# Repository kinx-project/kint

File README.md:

The kinT keyboard controller is a replacement for your Kinesis Advantage or
Advantage 2 ergonomic keyboards.

You can use it for example…

* to build or modify your own keyboard
* to [work around bugs in the standard controller](https://michael.stapelberg.ch/posts/2013-03-21-kinesis_custom_controller/)
* to resurrect a keyboard with a failing Kinesis keyboard controller
* because you prefer to run open source software such as the [QMK firmware](https://docs.qmk.fm/), even on your keyboard

See also:

* [My blog post introducing the kinT keyboard controller](https://michael.stapelberg.ch/posts/2020-07-09-kint-kinesis-keyboard-controller/)
* [My twitch stream recording introducing the kinT keyboard controller](https://youtu.be/I0kwQbnhlfk)

## Quick overview

<table border="0" width="100%">
<tr>
<td width="33%">

3D render (front, LEDs)
</td>
<td width="33%">

3D render (back, components)
</td>
<td width="33%">

schematic
</td>
</tr>
</table>

## Compatibility

The kinT keyboard controller was made for the Kinesis Advantage or Advantage 2
series.

The kinT keyboard controller is not compatible with the newer Kinesis Advantage
360 series, introduced in 2022, because the 360 is a split keyboard that uses an
entirely different form factor for its electronics ([Kinesis 360 teardown
photos](https://photos.app.goo.gl/BwgzHgaTz1RKBjqc6)).

The kinT keyboard controller is also not compatible with **very old Advantage**
keyboards, where the left and right keywell circuit boards plug directly into
the controller. See [issue #42](https://github.com/kinx-project/kint/issues/42)
for details and pictures.

## Building your own kinT keyboard controller

1. Follow [“Buying the board and components (Bill of
   materials)”](https://github.com/kinx-project/kint#buying-the-board-and-components-bill-of-materials). When
   ordering from OSH Park (board) and Digi-Key (components), you’ll get the
   minimum quantity of 3 boards for 72 USD (24 USD per board), and one set of
   components for 49 USD.

   * If you have any special requirements regarding which Teensy microcontroller
     to use, this is the step where you would replace the Teensy 3.6 with your
     choice.

1. Wait for the components to arrive. When ordering from big shops like Digi-Key
   or Mouser, this typically takes 2 days to many places in the world.

1. Wait for the boards to arrive. This takes 6 days in the best case when
   ordering from OSH Park with their Super Swift Service option. In general, the
   longer you are willing to wait, the cheaper it is going to get.

1. Follow [the soldering
   guide](https://github.com/kinx-project/kint#soldering). This will take about
   an hour.

1. [Install the firmware](https://github.com/kinx-project/kint#installing-the-firmware)

## Installing the kinT replacement controller in your Kinesis keyboard

After replacing your existing Kinesis controller with the kinT controller, you have some options with respect to the USB cable:

1. The easiest way is to remove the existing cable from the Kinesis keyboard, and
use a regular USB cable instead (going through the existing hole in the case, no
mod required).

1. If you want to keep using the existing Kinesis cable, you could build the [kinX
open hardware
hub](https://michael.stapelberg.ch/posts/2018-04-17-kinx-usb-hub/), which uses a
compatible connector.

1. Another way is to cut open a USB cable and solder it onto the matching pins of
the Kinesis cable.  You can confirm the pinout in the hardware design files for
the kinX hub. From issue #9, the [7-pin variant](https://github.com/kinx-project/kint/issues/9#issuecomment-751507493) and the [9-pin variant](https://github.com/kinx-project/kint/issues/9#issuecomment-774753427).

1. And yet one more option is to use a right angle USB dashboard extension instead of the Kinesis cable as described in [this issue #9 comment](https://github.com/kinx-project/kint/issues/9#issuecomment-1434304973). You would then plug a regular USB cable into this extension.

## Why use the kinT instead of the older replacement board?

* The kinT supports both, the older Kinesis Advantage (KB500) **and** the newer
  Kinesis Advantage 2 (KB600) keyboards. They differ in how the thumb pads are
  connected. See the soldering instructions below.

   * NOTE: If this is the *only* feature you’re interested in, and you already
     have a custom keyboard controller for your older Kinesis, [check out the
     u6w5 adapter
     board](https://github.com/kinx-project/adapter-use-kb600-with-kb500-controller)
     I made!

* The kinT is made for the newer Teensy 3.x and 4.x series, which will remain
  widely available for years to come, whereas the [Teensy++ 2.0 is
  discontinued](https://www.pjrc.com/store/teensypp.html).

* The kinT is a smaller PCB (4.25 x 3.39 inches, or 108.0 x 86.1 mm), which makes it:

   * more compact: can be inserted/removed without having to unscrew a key well.

   * cheaper: 72 USD for 3 boards at oshpark, instead of 81 USD.

* The kinT silkscreen
  ([front](https://raw.githubusercontent.com/kinx-project/kint/44e6c8be96a0e1e13ada5eafdeba8c51a2d6c9e8/pcb-3d-render-front-v2020-06-23.png),
  [back](https://raw.githubusercontent.com/kinx-project/kint/44e6c8be96a0e1e13ada5eafdeba8c51a2d6c9e8/pcb-3d-render-back-v2020-06-23.png))
  and
  [schematic](https://github.com/kinx-project/kint/blob/44e6c8be96a0e1e13ada5eafdeba8c51a2d6c9e8/schematic-v2020-06-23.pdf)
  are much much clearer, making assembly a breeze.

* The kinT is a good starting point for your own project:

   * kinT was designed in the open source [KiCad](https://kicad.org/)
     program, meaning you do not need any license subscriptions.

   * The clear silkscreen and schematic make development and debugging easier.

* On the kinT, the Teensy no longer has to be soldered onto the board upside down.

* On the kinT, the FPC connectors have been moved for less strain on the cables.

* The kinT makes possible lower-cost builds: if you don’t need the scroll lock,
  num lock and keypad LEDs, you can use a Teensy LC for merely 11 USD.

## Compatibility: which Teensy to use?

The kinT keyboard controller was made for the Teensy 3.x and 4.x series of
devices, which are ARM based.

The older Atmel based Teensy++ 2.0 are also supported, but they require cutting
one set of solder jumpers and closing a second set, to account for clashing pin
assignments.

Which Teensy should you buy for your build? Here are a few considerations:

* I have been using the Teensy 4.1 for many months without problems.

* I used the Teensy 3.6 for multiple years, and many others are happy with it,
  too.

* The Teensy++ 2.0 used to be the most popular choice, in part because it was
  the only option with the the predecessor keyboard controller. The [Teensy++
  2.0 is discontinued](https://www.pjrc.com/store/teensypp.html), so I would no
  longer recommend it for new keyboard builds.

* If you are an advanced user of the QMK firmware, note that despite QMK working
  on the Teensy 3.6, [some features are not yet
  ported/working](https://github.com/kinx-project/kint/issues/10). As QMK was
  originally made for AVR micro controllers, you will likely find best overall
  QMK feature availability with the older Teensy++ 2.0.

### Reference: full Teensy compatibility chart

TODO: add power consumption as a column. relevant for using the keyboard with a laptop on the go

| teensy         | LEDs | Cost   | input latency | clock speed | MCU         | QMK                                                                   |
|----------------|------|--------|---------------|-------------|-------------|-----------------------------------------------------------------------|
| teensy++ 2.0   | yes  | $24.00 | 3.27ms        | 16 MHz AVR  | AT90USB1286 | 0.13.17 or newer                                                      |
| ~~teensy 3.0~~ | no   |        |               | 48 MHz M4   | MK20DX128   | untested                                                              |
| ~~teensy 3.1~~ | no   |        |               |             | MK20DX256   | untested                                                              |
| teensy LC      | no   | $11.65 | ?             | 48 MHz M0+  |             | [development version](https://github.com/qmk/qmk_firmware/pull/17301) |
| teensy 3.2     | no   | $19.80 | ?             | 72 MHz M4   |             | [development version](https://github.com/qmk/qmk_firmware/pull/25013) |
| teensy 3.5     | yes  | $24.25 | ?             | 120 MHz M4F | MK64FX      | unlikely ([interest?](https://github.com/kinx-project/kint/issues/3)) |
| teensy 3.6     | yes  | $29.25 | 1.97ms        | 180 MHz M4F | MK66FX      | 0.14.0 or newer                                                       |
| teensy 4.0     | no   | $19.95 | 0.9ms         | 600 MHz M7  | MIMXRT1062  | 0.14.0 or newer                                                       |
| teensy 4.1     | yes  | $26.85 | 0.9ms         | 600 MHz M7  | MIMXRT1062  | 0.14.0 or newer                                                       |

See [this blog post for more details on keyboard input
latency](https://michael.stapelberg.ch/posts/2021-05-08-keyboard-input-latency-qmk-kinesis/).

## Buying the board and components (Bill of materials)

To buy the board, you can:

* [order the kinT controller from OSH Park](https://oshpark.com/shared_projects/YSZAuKc0) starting at 72 USD
* [order the kinT controller from Aisler](https://aisler.net/p/JQIIIJSL) starting at 18 EUR
* [order the kinT controller from JLCPCB](https://github.com/kinx-project/kint/tree/main/gerbers/jlcpcb)
* or upload the [kint.kicad_pcb
  file](https://github.com/kinx-project/kint/blob/main/kicad/kint.kicad_pcb)
  to the manufacturing service you prefer.

To buy the components, check out the [kinT BOM in the Octopart BOM
tool](https://octopart.com/bom-tool/4AnOAR3f), from where you can conveniently
buy all components via Digi-Key or Mouser.

For your convenience, this is the full BOM (links go to Octopart):

| Part Number                                                                               | Count | Cost   | Description               | Note                                               |
|-------------------------------------------------------------------------------------------|-------|--------|---------------------------|----------------------------------------------------|
| [Teensy 3.6](https://octopart.com/dev-14057-sparkfun-76356774?r=sp)                       | 1     | $32.5  |                           | [your choice!](#compatibility-which-teensy-to-use) |
| [Würth 61301011121](https://octopart.com/61301011121-w%C3%BCrth+elektronik-18818159?r=sp) | 8     | $0.89  | 10 position 2.54mm header | 6 for Teensy<br>2 for KB500<br>0 for KB600         |
| [Molex 39-53-2135](https://octopart.com/39-53-2135-molex-7670149?r=sp)                    | 6     | $1.24  | 13 position FPC connector | 4 for KB500<br>6 for KB600                         |
| [Kingbright APT3216QBC/D](https://octopart.com/apt3216qbc%2Fd-kingbright-5355642?r=sp)    | 4     | $0.47  | 1206 SMD LED              | blue 470nm<br>chose your color!                    |
| [Vishay CRCW120610K0FKEAC](https://octopart.com/crcw120610k0fkeac-vishay-20811529)        | 4     | $0.10  | 1206 10K resistor         | value determines LED brightness                    |
|                                                                                           |       | $48.45 |                           |                                                    |

Note: with all parts (except for the Molex 39-53-2135 FPC connector), there is
no need to get the specific versions from the BOM above — if you have LEDs,
resistors and pin headers still lying around from other projects, feel free to
re-use them!

Note: if you lost the original ribbon cables, you can get a compatible
replacement from [Digikey (Molex 13 Position FFC, FPC Cable 0.049" (1.25mm)
3.000"
(76.20mm))](https://www.digikey.co.uk/en/products/detail/molex/0151680815/4143332),
which is slightly longer than the original (CivLux E208903 - AWM 20960 105C 300V
VW-1), but seems to work well.

## Soldering

All the soldering connections on the kinT keyboard controller are easy to make,
so the whole assembly can be done at home, with a cheap soldering iron and basic
electronic hobby equipment. A build takes about 1 hour of time and involves a
little over 100 soldering connections.

For example, I used the [Miniware TS100 soldering
iron](https://hackaday.com/2017/07/24/review-ts100-soldering-iron/), which can
be found for 50-60 EUR or USD.

If you’re new to soldering, check out [this excellent soldering reference card
from adafruit](https://twitter.com/zekjur/status/952596267884056576).

You can also [watch me solder a kinT keyboard controller on live
stream](https://youtu.be/I0kwQbnhlfk?t=5880) (from 1:38:00 to 3:33:53). The
process can be done in under an hour if you’re not talking to a live audience at
the same time :-). I want to add an edited and higher-quality video, too.

### Soldering instructions for the Teensy 3.x or 4.x

1. Populate the FPC connectors J2, J3, J4, J7 (all keyboards) and J1, J8 for the
   newer Advantage 2 (KB600). Turn the board around and solder all their pins.

1. Solder resistors R1, R2, R3, R4 and the four LEDs onto the board.

   * LEDs are directional parts! Their marker marks the cathode, which is
     labeled as C on the kinT. For details about the marker, refer to the LED
     datasheet, e.g. the [Kingbright APT3216QBC/D data
     sheet](https://www.kingbrightusa.com/images/catalog/SPEC/APT3216QBC-D.pdf)
     if you are using the LED from the [Bill of Materials
     (BOM)](#buying-the-board-and-components-bill-of-materials).

   * If you’re new to SMD (Surface Mount Devices) soldering, check out [How to
     Hand Solder SMD](http://www.davidhaillant.com/smd-soldering/), which
     explains what I call the “One pad at a time” method.

1. Turn the board around and place (but don’t solder) **3 rows of pin headers**
   (top, bottom, vertical) in the Teensy holes.

   * The vertical pin header is required for powering the LEDs.

   * If you want your Teensy to be removable, you can use socket headers here
     instead. [See the instructions below](#using-socket-headers).

1. Place your Teensy on top of the pin header and solder all its pins.

1. Turn the board around and solder all the pin header pins.

1. For the older Advantage (KB500) keyboard, populate pin headers J5, J6 and
   solder their pins.

### Soldering instructions for the Teensy++ 2.0

Follow the [instructions for the Teensy 3.x or 4.x
above](#soldering-instructions-for-the-teensy-3x-or-4x), and then:

1. Using a small knife such as a hobby knife, cut the traces between the pads
   of jumpers JP4, JP5, and JP6. This will disconnect pin 7, pin 15 and pin 16.

   * If you haven't cut traces like this before, SparkFun has a [brief
     illustrated tutorial][jumper-tut] about working with jumpers that is a
     good reference.

2. Close the solder jumpers JP1, JP2, JP3. These will remap pin 7, pin 15 and
   pin 16 onto pins that can be used with the Teensy++ 2.0.

If you are [using socket headers](#using-socket-headers) so that the Teensy is
removable, you can later upgrade to a Teensy 3.x or 4.x by desoldering JP1,
JP2, and JP3, and reclosing the jumpers JP4, JP5, and JP6.

[jumper-tut]: https://learn.sparkfun.com/tutorials/how-to-work-with-jumper-pads-and-pcb-traces/what-is-a-jumper

### Using socket headers

Due to the space for the USB cable in the back, there's not enough room in the
case for a standard socket header, but there are low-profile pin headers that
do fit. [These square-pin socket headers][short-sockets] and [pins][short-pins]
with 0.180" (4.57mm) insulation height have been verified to fit in the KB500,
and will probably fit the KB600 as well. Round "Swiss-style" headers may also
work, but make sure to get the appropriate matching pins for whatever socket
you order.

To build with socket headers, follow the [standard instructions
above](#soldering-instructions-for-the-teensy-3x-or-4x), but instead of the
steps involving soldering the pin headers, do the following:

1. Turn the board around and solder **3 rows of socket headers** (top, bottom,
   vertical) in the Teensy holes on the kinT board.

1. Place and solder the corresponding **3 rows of pin headers** (top, bottom,
   vertical) on the Teensy itself.

1. Insert the Teensy into the sockets.

[short-sockets]: https://octopart.com/slw-124-01-t-s-samtec-292526?r=sp
[short-pins]: https://octopart.com/tsw-124-23-g-s-samtec-274217?r=sp

## Installing the firmware

You can use the QMK Configurator online build tool to compile the QMK firmware for
your kinT keyboard controller, or customize your layout.

Alternatively, you can install the pre-built, tested firmware file (default QMK
keymap and settings) we offer, for example to test whether issues are related to
your self-compiled firmware.

| Teensy           | QMK Configurator                                                                                                                                         | pre-built, tested firmware                                                                                                              |
|------------------|----------------------------------------------------------------------------------------------------------------------------------------------------------|-----------------------------------------------------------------------------------------------------------------------------------------|
| Teensy++ 2.0     | [QMK Configurator (kint2pp)](https://config.qmk.fm/#/kinesis/kint2pp/LAYOUT)                                                                             | [kinesis_kint2pp_default.hex](https://github.com/kinx-project/kint/blob/main/default-firmware/kinesis_kint2pp_default.hex) (2020-07-09) |
| Teensy 3.6       | [QMK Configurator (kint36)](https://config.qmk.fm/#/kinesis/kint36/LAYOUT)                                                                               | [kinesis_kint36_default.hex](https://github.com/kinx-project/kint/blob/main/default-firmware/kinesis_kint36_default.hex) (2020-07-09)   |
| Teensy 4.0 / 4.1 | [QMK Configurator (kint41)](https://config.qmk.fm/#/kinesis/kint41/LAYOUT)  | [kinesis_kint41_default.hex](https://github.com/kinx-project/kint/blob/main/default-firmware/kinesis_kint41_default.hex) (QMK 0.17.9)   |

You can install these .hex files with the [Teensy
Loader](https://www.pjrc.com/teensy/loader.html).

To compile your own firmware, see [QMK: Get
Started](https://docs.qmk.fm/#/?id=get-started) and refer to the [full Teensy
compatibility chart](#reference-full-teensy-compatibility-chart) above to find
the QMK branch to work with.

TIP: When you flash your Teensy you'll be asked to press the reset button. The first time you flash, you'll need to press the push button on the Teensy itself. Default keyboard layouts map this ability to the Kinesis <kbd>progm</kbd> key. So for subsequent flashes, you can press the <kbd>progm</kbd> key instead.

## Debugging / Troubleshooting

### General technique: highlight connections in KiCad

1. Install [KiCad](https://kicad.org/) (free and open source)
1. Clone https://github.com/kinx-project/kint/ and open `kicad/kint.pro` in KiCad
1. Select `Tools` → `Edit PCB`
1. Select `View` → `Flip Board View`, because the front side of kinT contains the LEDs, the back side contains the connectors.
1. Select `Highlight Net`, the second icon from the top in the right icon bar.
   In KiCad 6, the icon is gone. Instead, hold the `Ctrl` key while clicking on the net.
1. Click on the pin of interest. In the bottom left, you’ll see the Net Name (e.g. `COL_3`), and KiCad will highlight all connected traces.

### Issue: LEDs not working

See also [Example issue #13](https://github.com/kinx-project/kint/issues/13) for
a full debugging walk-through.

* Check the orientation of your LEDs, as they are directional parts.

   * The marker printed on the kinT board marks the LED cathode, which is
     labeled as C on the kinT. For details about the marker, refer to the LED
     datasheet, e.g. the [Kingbright APT3216QBC/D data
     sheet](https://www.kingbrightusa.com/images/catalog/SPEC/APT3216QBC-D.pdf)
     if you are using the LED from the [Bill of Materials
     (BOM)](#buying-the-board-and-components-bill-of-materials).

* If your Teensy is not soldered yet (or removed from its socket), you can test your LEDs with a multimeter:
   * switch your multimeter to diode test mode
   * place the black probe (`COM`) on e.g. Teensy pin 12 (`LED_CAPS_LOCK`)
   * place the red probe on the anode (A) of your LED
   * the LED should light up now, or it might be defective:

* Measure that the LED pins behave as expected, e.g. Teensy pin 12 for `LED_CAPS_LOCK`:
   * you should measure 3.3V when the LED is turned off
   * you should measure 0V when the LED is turned on

* Check that you soldered in the vertical pin header, which supplies 3.3V to the LEDs:

### Issue: Keys not working
If groups of keys are not responding, recheck that you've inserted cables straight and deep into each Molex connector before fully closing the connector.

See also [issue #16](https://github.com/kinx-project/kint/issues/16) for
a full debugging walk-through of key issues.

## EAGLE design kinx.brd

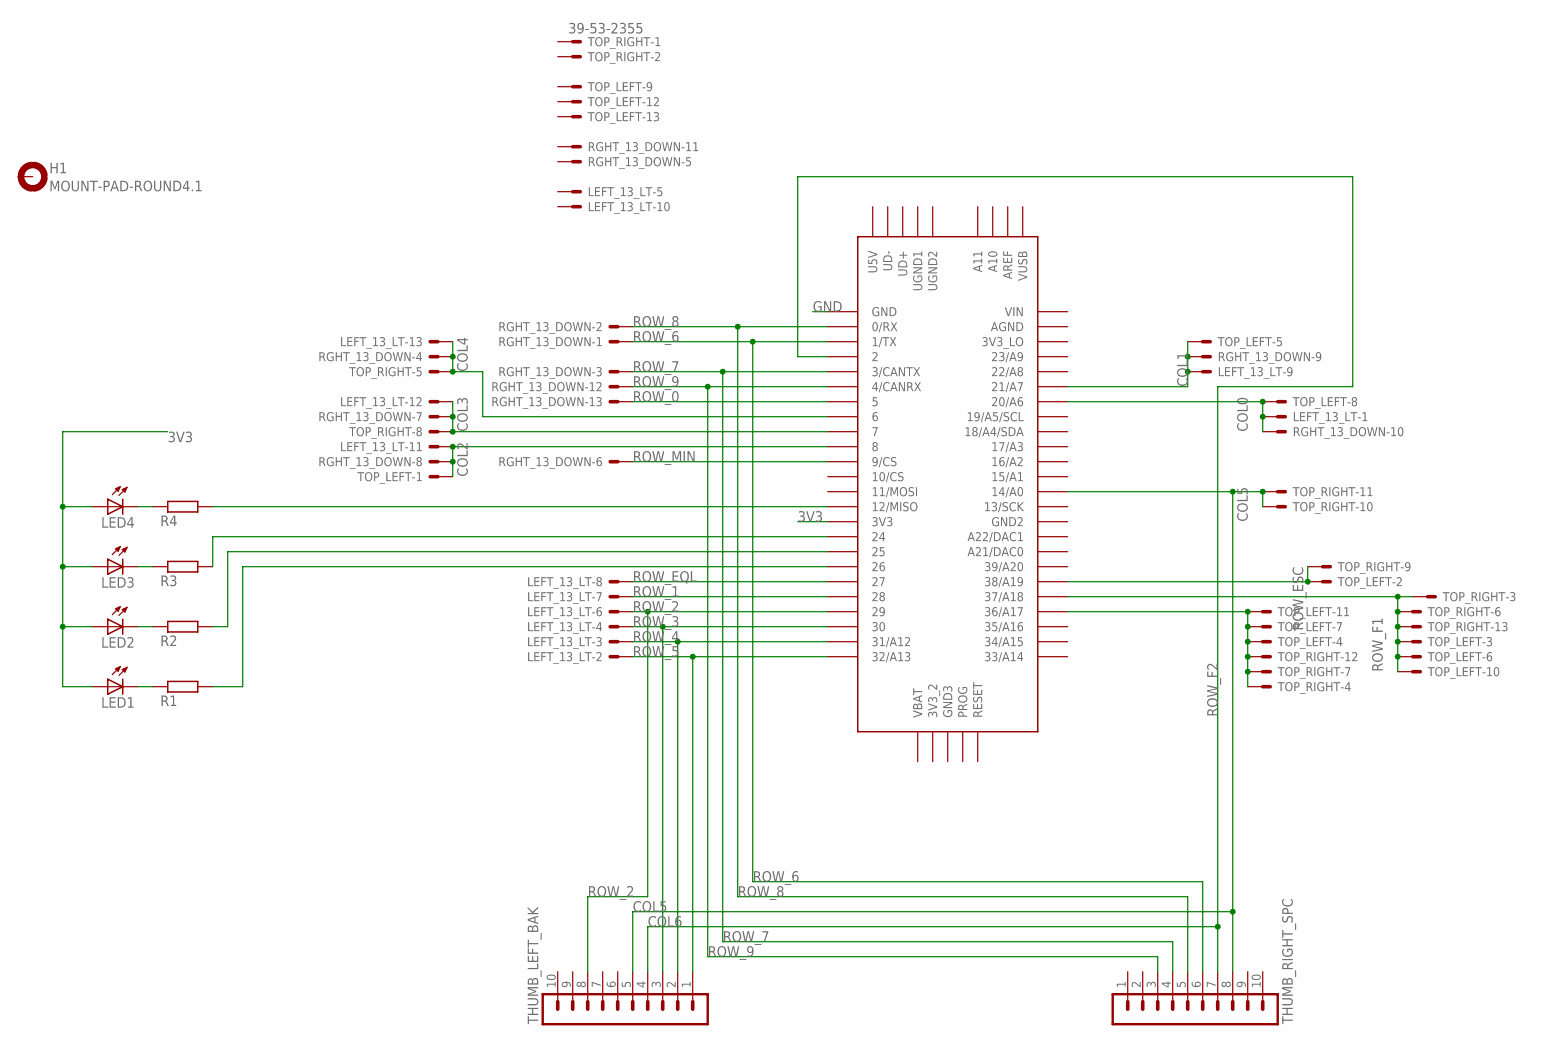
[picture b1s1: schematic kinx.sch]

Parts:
H1: MOUNT-PAD-ROUND4.1; 4,1-PAD
LED1, LED2, LED3, LED4: LEDSML1206; SML1206
LEFT_13_LT: 39-53-2355; 39-53-2135
R1, R2, R3, R4: R-EU_R1206; R1206
RGHT_13_DOWN: 39-53-2355; 39-53-2135
THUMB_LEFT_BAK: MA10-1
THUMB_RIGHT_SPC: MA10-1
TOP_LEFT: 39-53-2355; 39-53-2135
TOP_RIGHT: 39-53-2355; 39-53-2135
U1: TEENSY_3.5/3.6

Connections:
3V3: LED1.A, LED2.A, LED3.A, LED4.A, U1.3V3
COL0: LEFT_13_LT.P$1, RGHT_13_DOWN.P$10, TOP_LEFT.P$8, U1.20/A6
COL1: LEFT_13_LT.P$9, RGHT_13_DOWN.P$9, TOP_LEFT.P$5, U1.21/A7
COL2: LEFT_13_LT.P$11, RGHT_13_DOWN.P$8, TOP_LEFT.P$1, U1.8
COL3: LEFT_13_LT.P$12, RGHT_13_DOWN.P$7, TOP_RIGHT.P$8, U1.7
COL4: LEFT_13_LT.P$13, RGHT_13_DOWN.P$4, TOP_RIGHT.P$5, U1.6
COL5: THUMB_LEFT_BAK.5, THUMB_RIGHT_SPC.8, TOP_RIGHT.P$10, TOP_RIGHT.P$11, U1.14/A0
COL6: THUMB_LEFT_BAK.4, THUMB_RIGHT_SPC.7, U1.2
GND: U1.GND
unnamed: R4.2, U1.12/MISO
unnamed: R3.2, U1.24
unnamed: R2.2, U1.25
unnamed: R1.2, U1.26
unnamed: LED4.C, R4.1
unnamed: LED3.C, R3.1
unnamed: LED2.C, R2.1
unnamed: LED1.C, R1.1
ROW_0: RGHT_13_DOWN.P$13, U1.5
ROW_1: LEFT_13_LT.P$7, U1.28
ROW_2: LEFT_13_LT.P$6, THUMB_LEFT_BAK.8, U1.29
ROW_3: LEFT_13_LT.P$4, THUMB_LEFT_BAK.3, U1.30
ROW_4: LEFT_13_LT.P$3, THUMB_LEFT_BAK.2, U1.31/A12
ROW_5: LEFT_13_LT.P$2, THUMB_LEFT_BAK.1, U1.32/A13
ROW_6: RGHT_13_DOWN.P$1, THUMB_RIGHT_SPC.6, U1.1/TX
ROW_7: RGHT_13_DOWN.P$3, THUMB_RIGHT_SPC.4, U1.3/CANTX
ROW_8: RGHT_13_DOWN.P$2, THUMB_RIGHT_SPC.5, U1.0/RX
ROW_9: RGHT_13_DOWN.P$12, THUMB_RIGHT_SPC.3, U1.4/CANRX
ROW_EQL: LEFT_13_LT.P$8, U1.27
ROW_ESC: TOP_LEFT.P$2, TOP_RIGHT.P$9, U1.38/A19
ROW_F1: TOP_LEFT.P$3, TOP_LEFT.P$6, TOP_LEFT.P$10, TOP_RIGHT.P$3, TOP_RIGHT.P$6, TOP_RIGHT.P$13, U1.37/A18
ROW_F2: TOP_LEFT.P$4, TOP_LEFT.P$7, TOP_LEFT.P$11, TOP_RIGHT.P$4, TOP_RIGHT.P$7, TOP_RIGHT.P$12, U1.36/A17
ROW_MIN: RGHT_13_DOWN.P$6, U1.9/CS

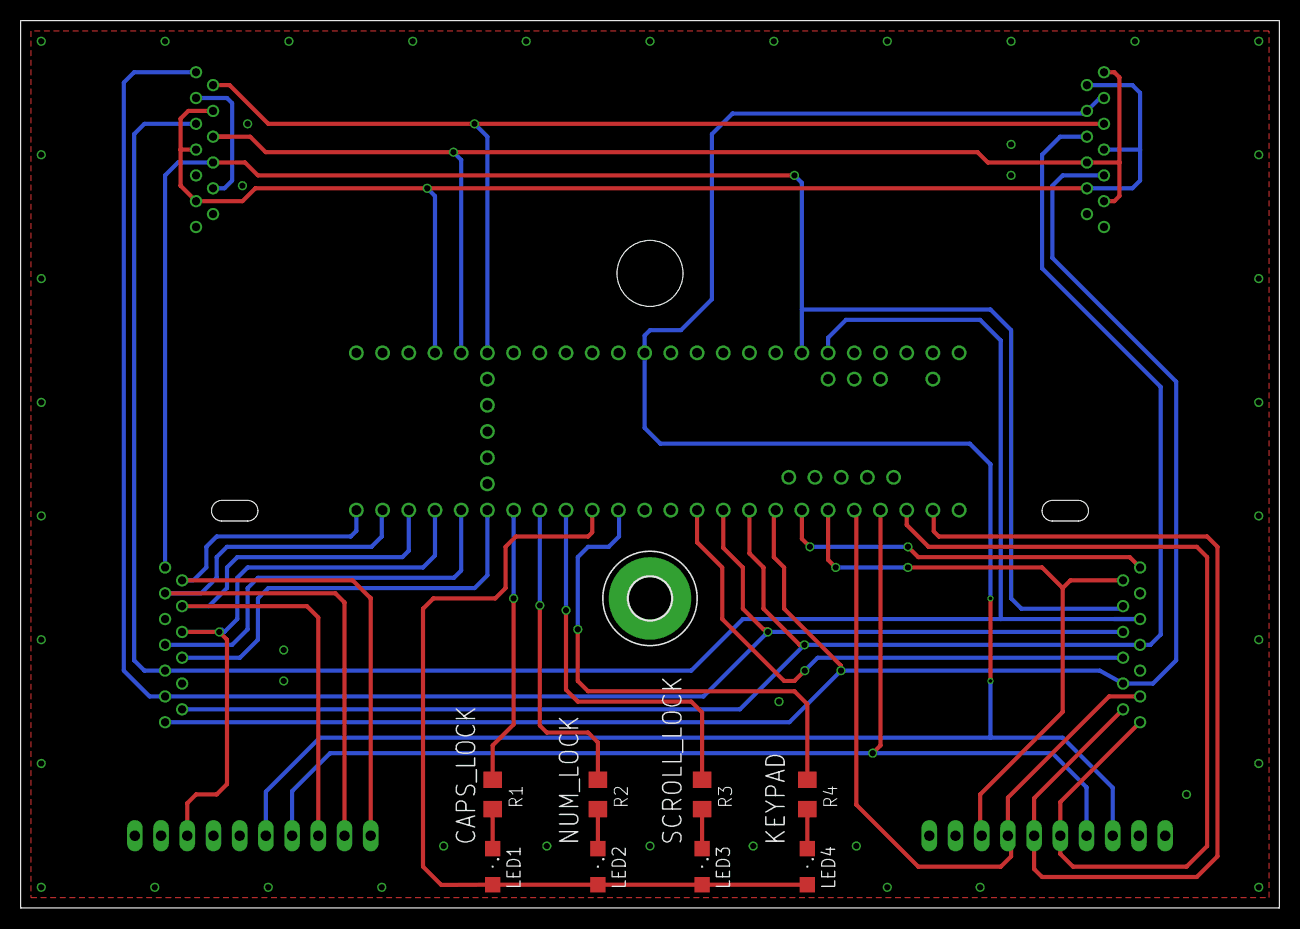
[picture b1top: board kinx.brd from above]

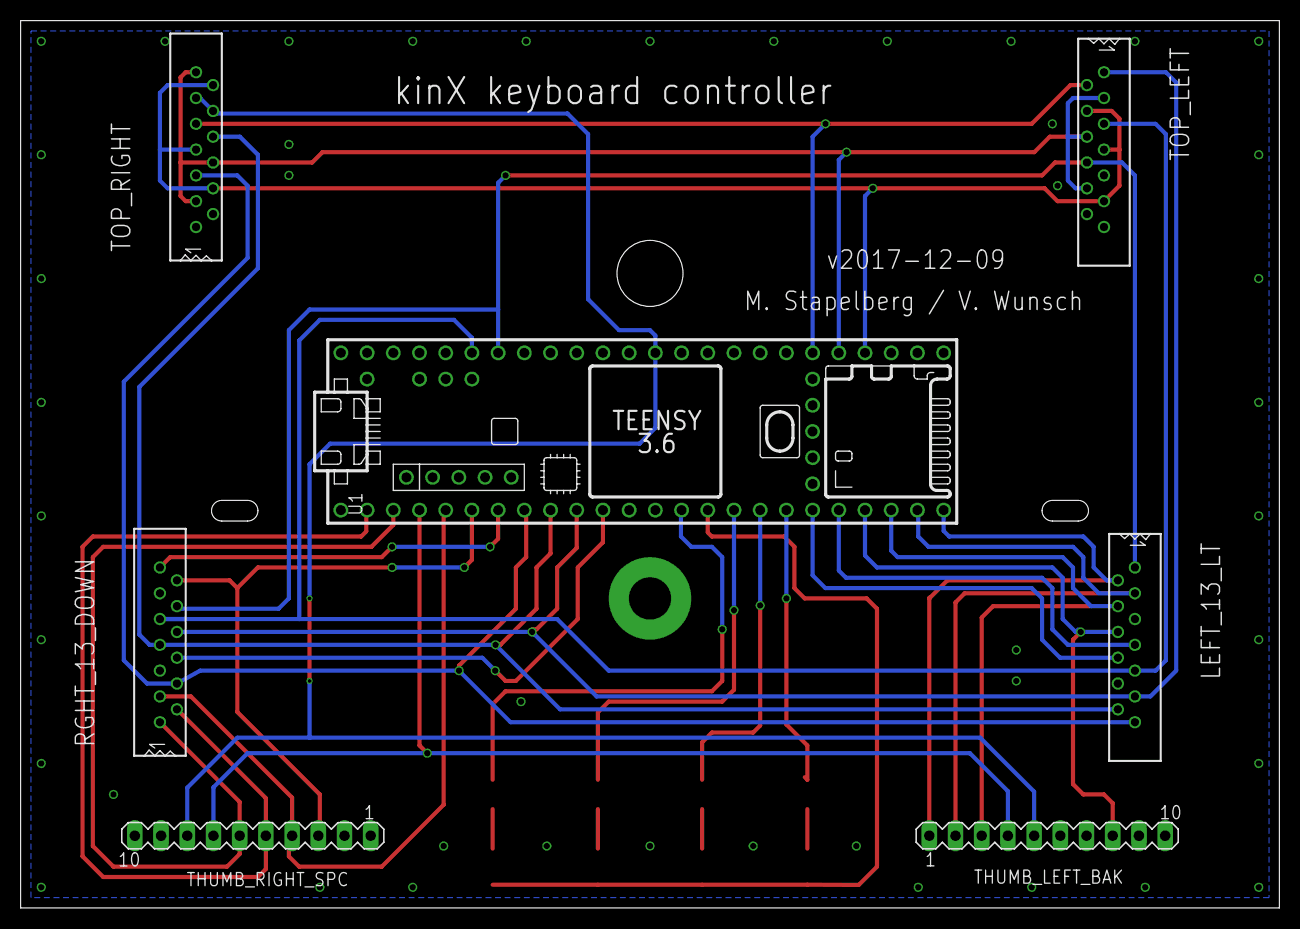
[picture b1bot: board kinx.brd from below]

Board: 2 copper layers, 122.0 x 86.0 mm, 16 parts (7 on the bottom side), 31 nets.

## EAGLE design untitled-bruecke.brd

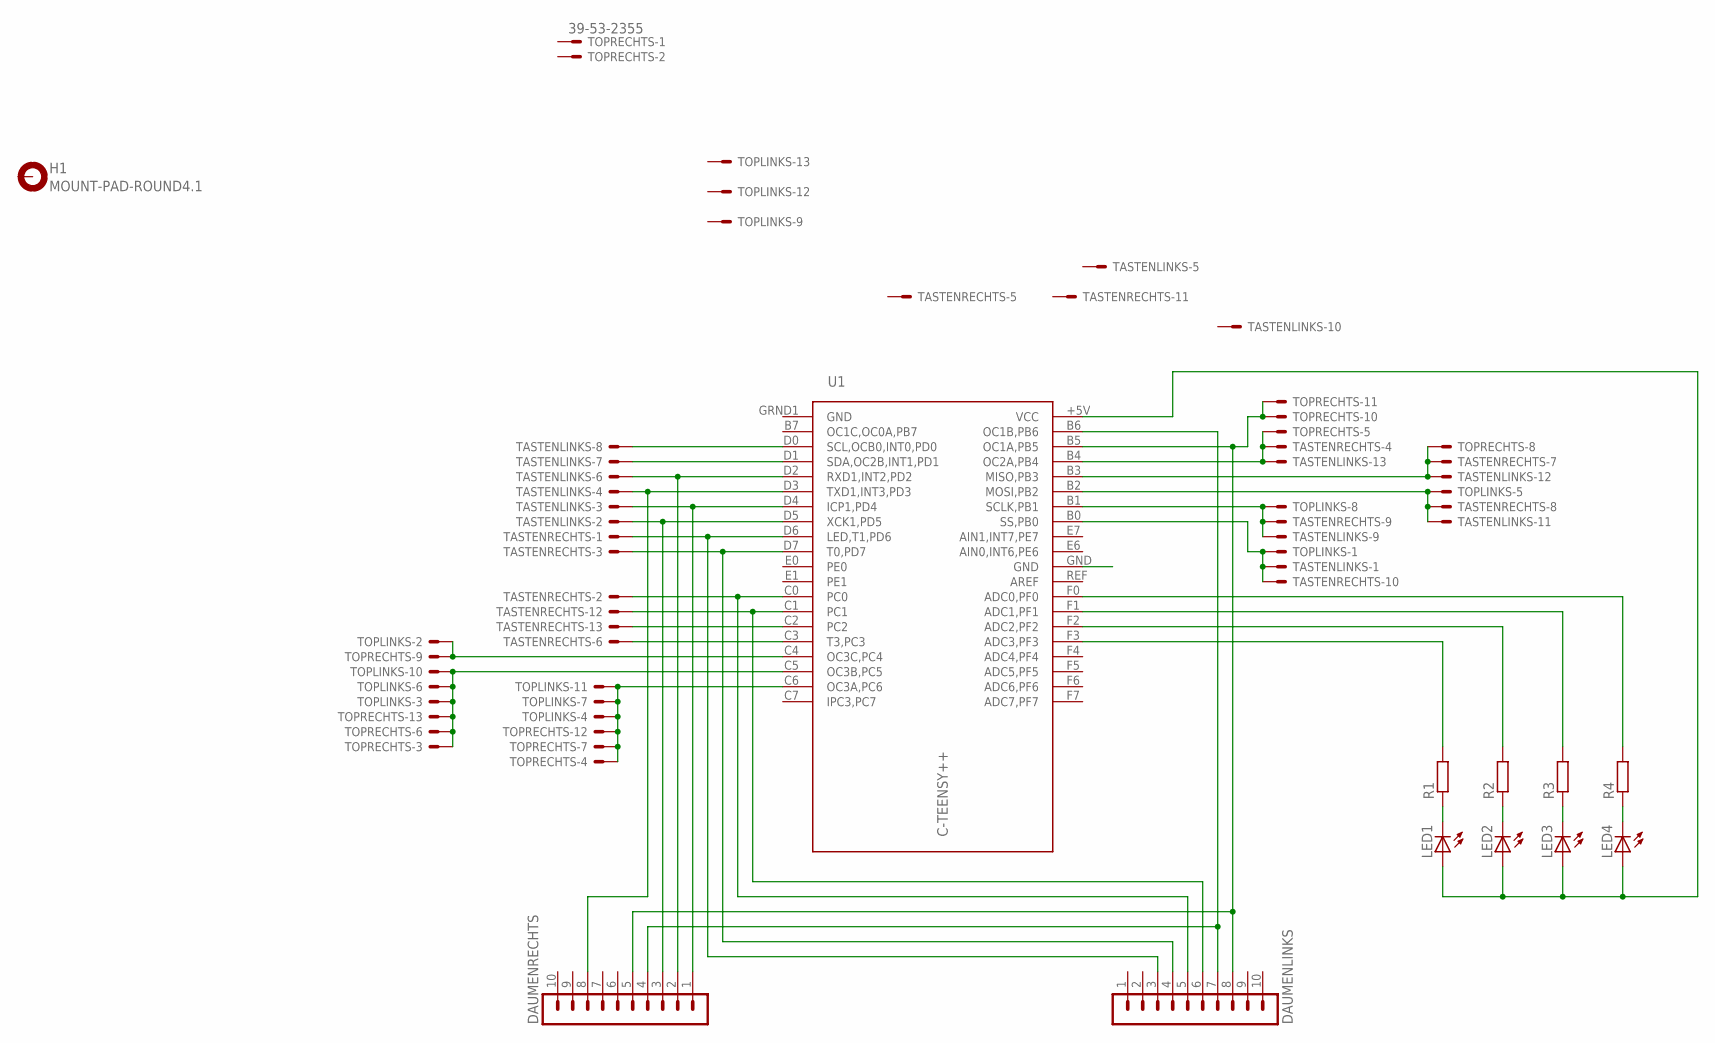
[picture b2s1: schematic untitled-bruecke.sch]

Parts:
DAUMENLINKS: MA10-1
DAUMENRECHTS: MA10-1
H1: MOUNT-PAD-ROUND4.1; 4,1-PAD
LED1, LED2, LED3, LED4: LED3MM
R1, R2, R3, R4: R-EU_R1206; R1206
TASTENLINKS: 39-53-2355; 39-53-2135
TASTENRECHTS: 39-53-2355; 39-53-2135
TOPLINKS: 39-53-2355; 39-53-2135
TOPRECHTS: 39-53-2355; 39-53-2135
U1: C-TEENSY++; TEENSY++

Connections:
B0: TASTENLINKS.P$1, TASTENRECHTS.P$10, TOPLINKS.P$1, U1.B0 (SS,PB0)
B1: TASTENLINKS.P$9, TASTENRECHTS.P$9, TOPLINKS.P$8, U1.B1 (SCLK,PB1)
B2: TASTENLINKS.P$11, TASTENRECHTS.P$8, TOPLINKS.P$5, U1.B2 (MOSI,PB2)
B3: TASTENLINKS.P$12, TASTENRECHTS.P$7, TOPRECHTS.P$8, U1.B3 (MISO,PB3)
B4: TASTENLINKS.P$13, TASTENRECHTS.P$4, TOPRECHTS.P$5, U1.B4 (OC2A,PB4)
B5: DAUMENLINKS.8, DAUMENRECHTS.5, TOPRECHTS.P$10, TOPRECHTS.P$11, U1.B5 (OC1A,PB5)
B6: DAUMENLINKS.7, DAUMENRECHTS.4, U1.B6 (OC1B,PB6)
C0: DAUMENLINKS.5, TASTENRECHTS.P$2, U1.C0
C1: DAUMENLINKS.6, TASTENRECHTS.P$12, U1.C1
C2: TASTENRECHTS.P$13, U1.C2
C3: TASTENRECHTS.P$6, U1.C3 (T3,PC3)
C4: TOPLINKS.P$2, TOPRECHTS.P$9, U1.C4 (OC3C,PC4)
C5: TOPLINKS.P$3, TOPLINKS.P$6, TOPLINKS.P$10, TOPRECHTS.P$3, TOPRECHTS.P$6, TOPRECHTS.P$13, U1.C5 (OC3B,PC5)
C6: TOPLINKS.P$4, TOPLINKS.P$7, TOPLINKS.P$11, TOPRECHTS.P$4, TOPRECHTS.P$7, TOPRECHTS.P$12, U1.C6 (OC3A,PC6)
D0: TASTENLINKS.P$8, U1.D0 (SCL,OCB0,INT0,PD0)
D1: TASTENLINKS.P$7, U1.D1 (SDA,OC2B,INT1,PD1)
D2: DAUMENRECHTS.2, TASTENLINKS.P$6, U1.D2 (RXD1,INT2,PD2)
D3: DAUMENRECHTS.8, TASTENLINKS.P$4, U1.D3 (TXD1,INT3,PD3)
D4: DAUMENRECHTS.1, TASTENLINKS.P$3, U1.D4 (ICP1,PD4)
D5: DAUMENRECHTS.3, TASTENLINKS.P$2, U1.D5 (XCK1,PD5)
D6: DAUMENLINKS.3, TASTENRECHTS.P$1, U1.D6 (LED,T1,PD6)
D7: DAUMENLINKS.4, TASTENRECHTS.P$3, U1.D7 (T0,PD7)
GND: U1.GRND1 (GND)
unnamed: R1.2, U1.F3 (ADC3,PF3)
unnamed: R2.2, U1.F2 (ADC2,PF2)
unnamed: R3.2, U1.F1 (ADC1,PF1)
unnamed: R4.2, U1.F0 (ADC0,PF0)
unnamed: LED1.A, LED2.A, LED3.A, LED4.A, U1.+5V (VCC)
unnamed: LED4.K (C), R4.1
unnamed: LED3.K (C), R3.1
unnamed: LED2.K (C), R2.1
unnamed: LED1.K (C), R1.1

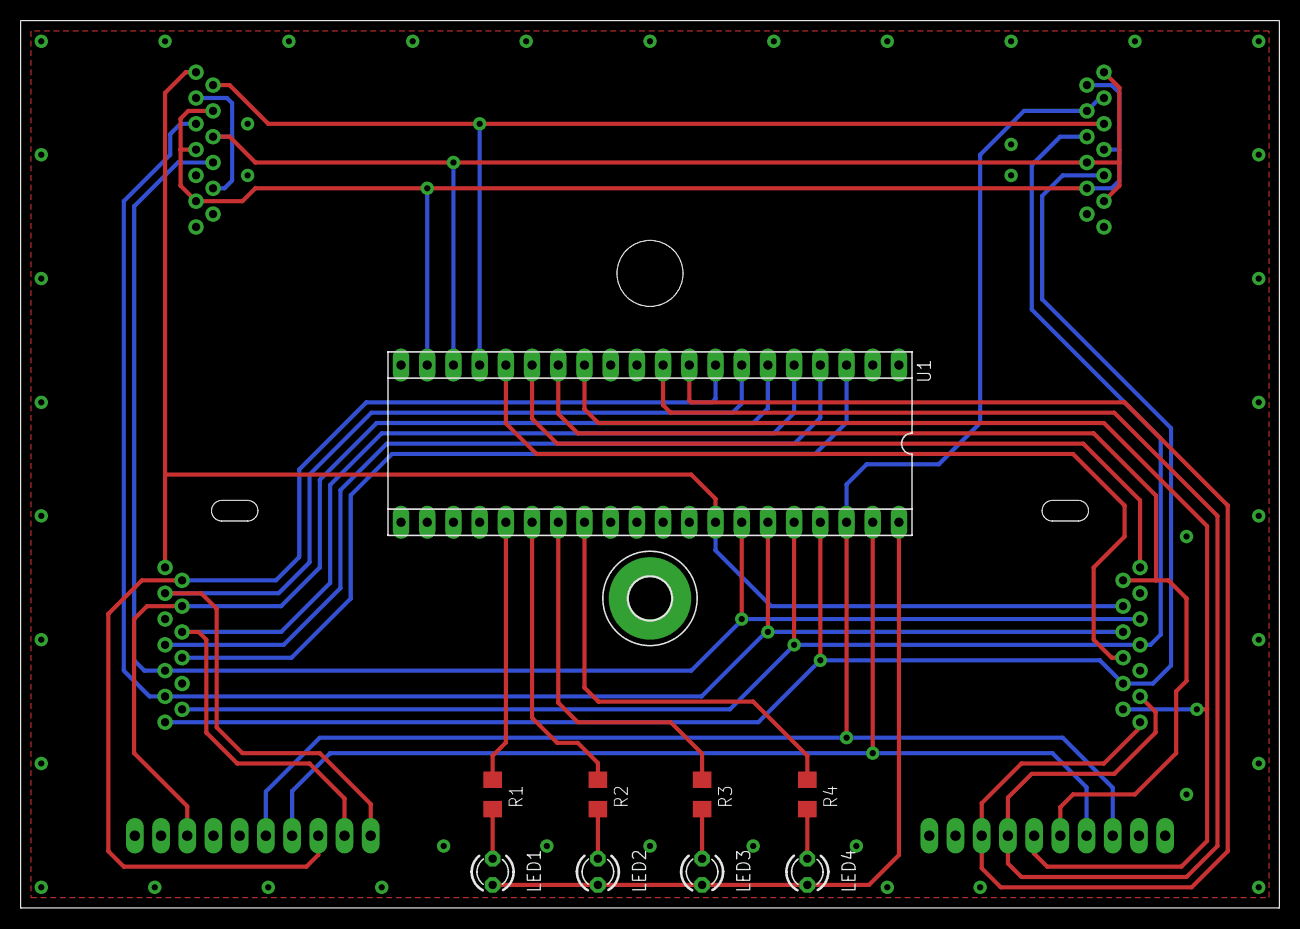
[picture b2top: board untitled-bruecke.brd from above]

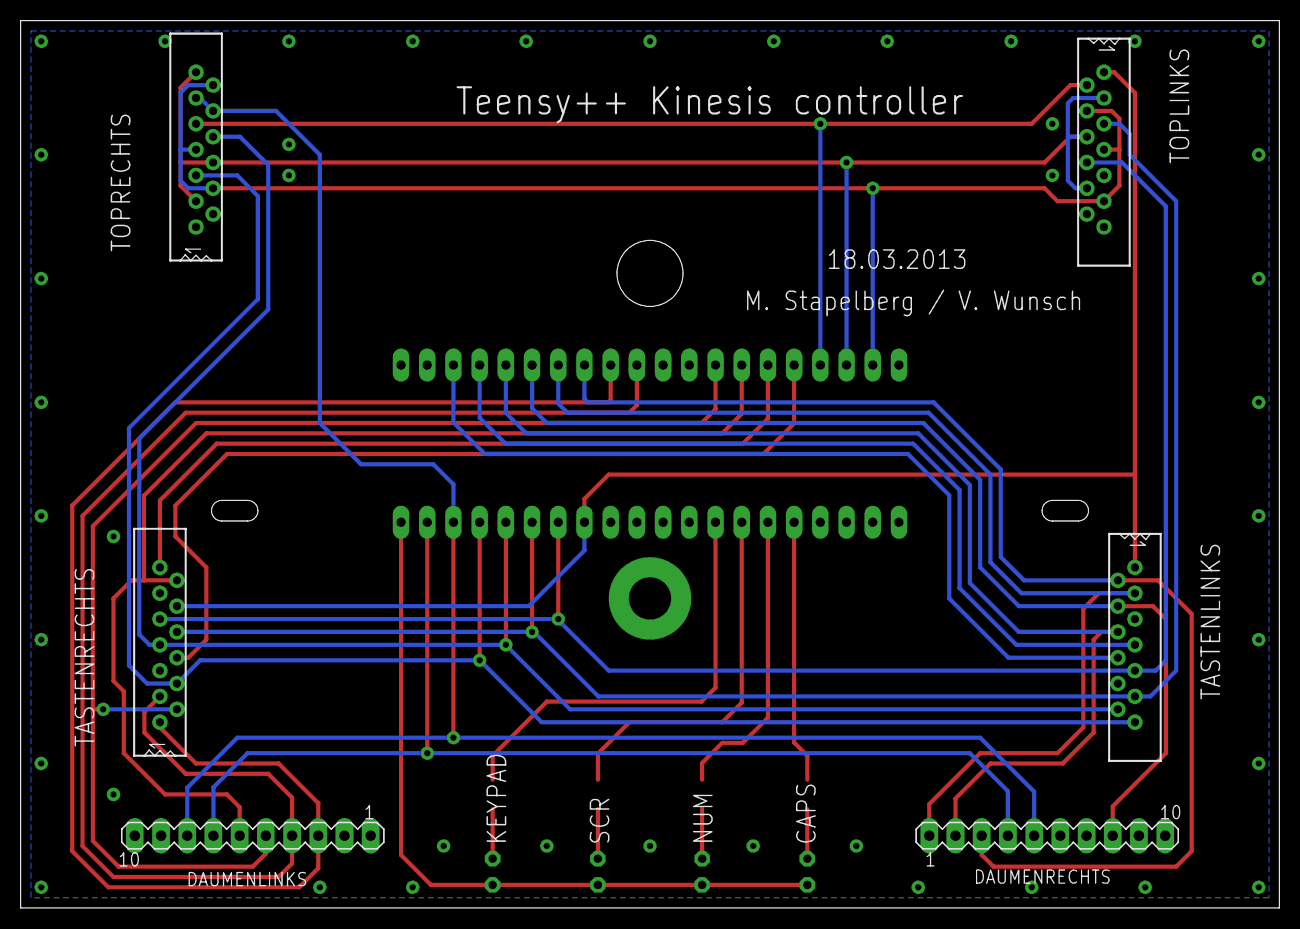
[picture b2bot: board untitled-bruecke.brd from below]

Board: 2 copper layers, 122.0 x 86.0 mm, 16 parts (6 on the bottom side), 31 nets.

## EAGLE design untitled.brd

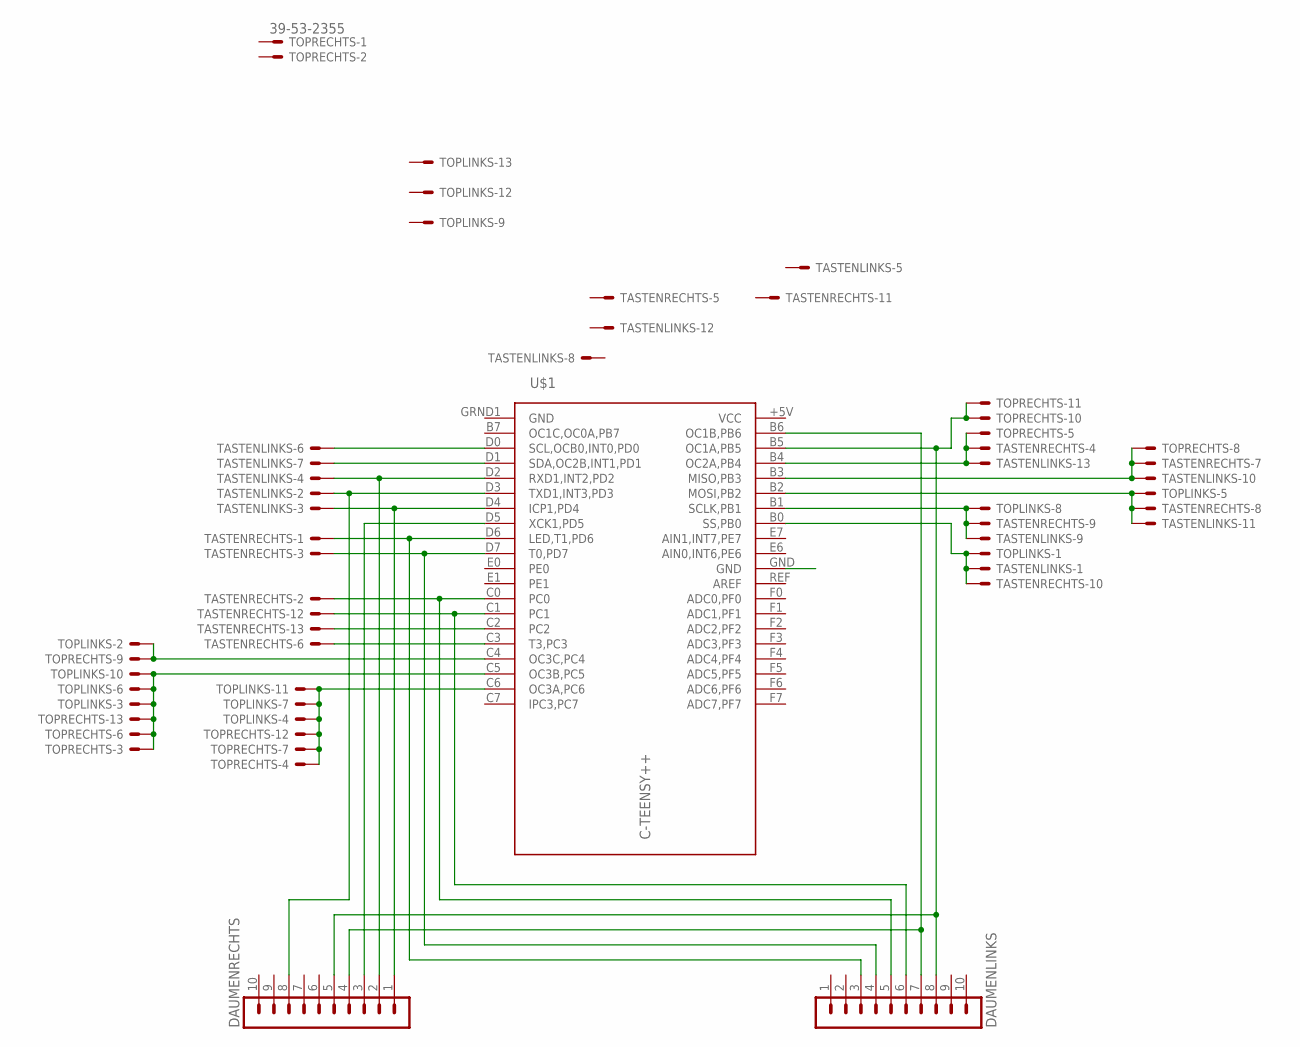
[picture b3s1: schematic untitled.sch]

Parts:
DAUMENLINKS: MA10-1
DAUMENRECHTS: MA10-1
TASTENLINKS: 39-53-2355; 39-53-2135
TASTENRECHTS: 39-53-2355; 39-53-2135
TOPLINKS: 39-53-2355; 39-53-2135
TOPRECHTS: 39-53-2355; 39-53-2135
U$1: C-TEENSY++; TEENSY++

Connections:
B0: TASTENLINKS.P$1, TASTENRECHTS.P$10, TOPLINKS.P$1, U$1.B0 (SS,PB0)
B1: TASTENLINKS.P$9, TASTENRECHTS.P$9, TOPLINKS.P$8, U$1.B1 (SCLK,PB1)
B2: TASTENLINKS.P$11, TASTENRECHTS.P$8, TOPLINKS.P$5, U$1.B2 (MOSI,PB2)
B3: TASTENLINKS.P$10, TASTENRECHTS.P$7, TOPRECHTS.P$8, U$1.B3 (MISO,PB3)
B4: TASTENLINKS.P$13, TASTENRECHTS.P$4, TOPRECHTS.P$5, U$1.B4 (OC2A,PB4)
B5: DAUMENLINKS.8, DAUMENRECHTS.5, TOPRECHTS.P$10, TOPRECHTS.P$11, U$1.B5 (OC1A,PB5)
B6: DAUMENLINKS.7, DAUMENRECHTS.4, U$1.B6 (OC1B,PB6)
C0: DAUMENLINKS.5, TASTENRECHTS.P$2, U$1.C0
C1: DAUMENLINKS.6, TASTENRECHTS.P$12, U$1.C1
C2: TASTENRECHTS.P$13, U$1.C2
C3: TASTENRECHTS.P$6, U$1.C3 (T3,PC3)
C4: TOPLINKS.P$2, TOPRECHTS.P$9, U$1.C4 (OC3C,PC4)
C5: TOPLINKS.P$3, TOPLINKS.P$6, TOPLINKS.P$10, TOPRECHTS.P$3, TOPRECHTS.P$6, TOPRECHTS.P$13, U$1.C5 (OC3B,PC5)
C6: TOPLINKS.P$4, TOPLINKS.P$7, TOPLINKS.P$11, TOPRECHTS.P$4, TOPRECHTS.P$7, TOPRECHTS.P$12, U$1.C6 (OC3A,PC6)
D0: TASTENLINKS.P$6, U$1.D0 (SCL,OCB0,INT0,PD0)
D1: TASTENLINKS.P$7, U$1.D1 (SDA,OC2B,INT1,PD1)
D2: DAUMENRECHTS.2, TASTENLINKS.P$4, U$1.D2 (RXD1,INT2,PD2)
D3: DAUMENRECHTS.8, TASTENLINKS.P$2, U$1.D3 (TXD1,INT3,PD3)
D4: DAUMENRECHTS.1, TASTENLINKS.P$3, U$1.D4 (ICP1,PD4)
D5: DAUMENRECHTS.3, U$1.D5 (XCK1,PD5)
D6: DAUMENLINKS.3, TASTENRECHTS.P$1, U$1.D6 (LED,T1,PD6)
D7: DAUMENLINKS.4, TASTENRECHTS.P$3, U$1.D7 (T0,PD7)
GND: U$1.GRND1 (GND)
VCC: U$1.+5V (VCC)

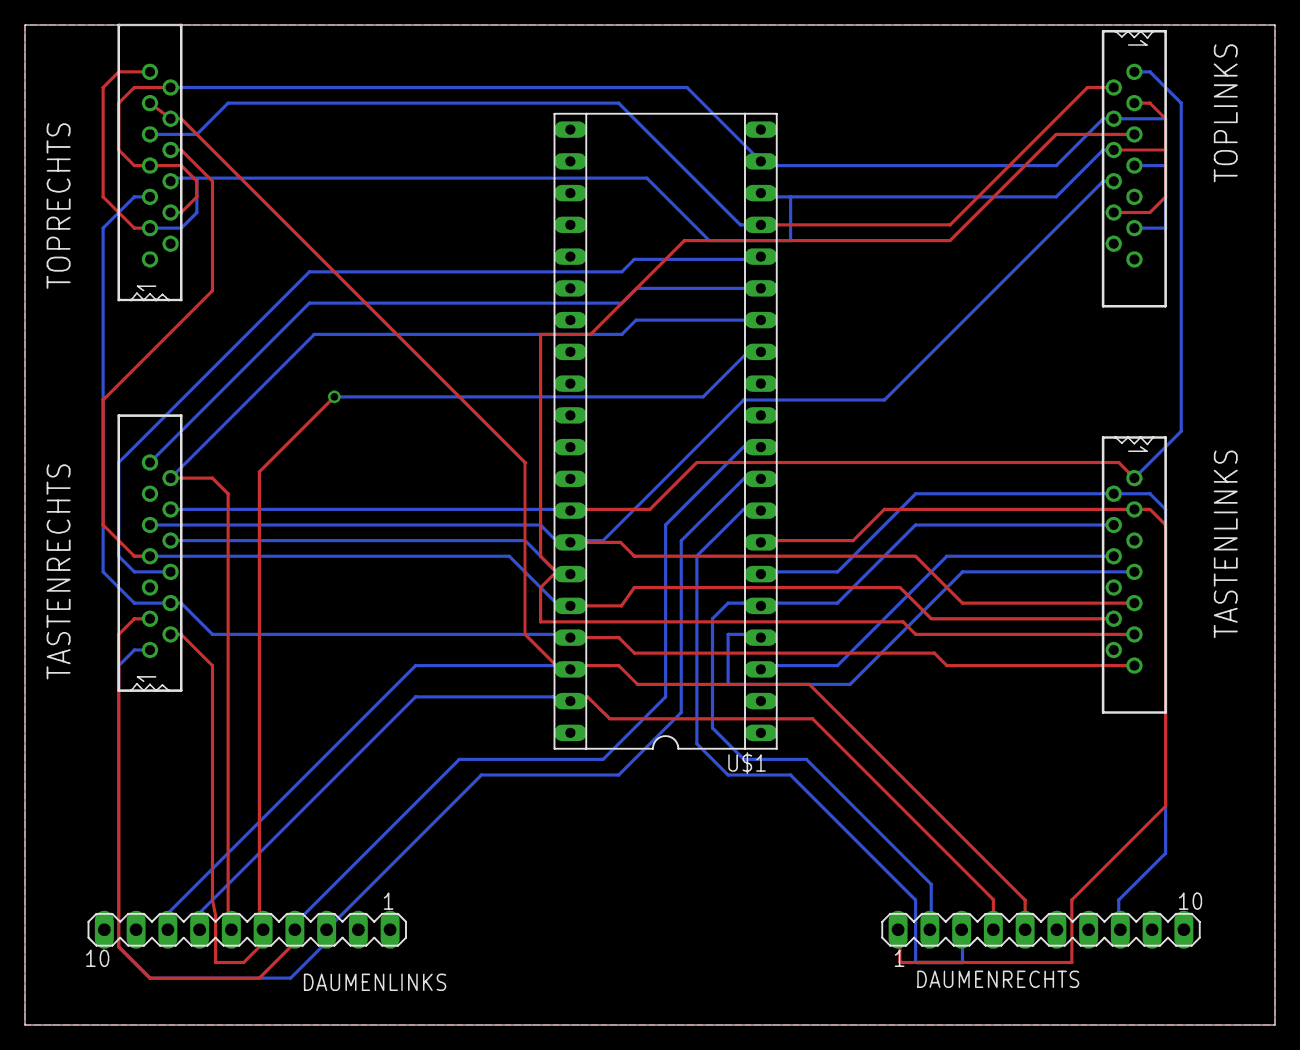
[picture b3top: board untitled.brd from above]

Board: 2 copper layers, 100.0 x 80.0 mm, 7 parts (0 on the bottom side), 22 nets.

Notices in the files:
README.md:
License: CC BY-SA 4.0
